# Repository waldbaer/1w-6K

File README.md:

# 1-Wire 6-Channel Binary Input Board using DS2411

A compact PCB providing six independent binary input channels on a 1-Wire bus, each based on a dedicated [DS2411](doc/ds2411.pdf) unique-ID device.
Prepared for use in standard 35 mm DIN-rail mounting enclosures.

## Hardware

### Schematic

see [1w-6K_schematic.pdf](doc/1w-6K_schematic.pdf).

### Rendering / Photo

### DIN-rail mounting

The PCB can be mounted to standard 35mm DIN rails using common _25mm DIN Rail Mounting Adapter_ with hole spacing of **12.5mm**.

## Key Features

* 6 × DS2411 devices connected to a the 1-Wire bus
  * Each DS2411 has its GND routed to an individual screw terminal.
  * A binary input channel is considered “closed” when its DS2411 (with factory-programmed 64-bit ROM ID) becomes visible on the bus.

* 1 additional DS2411 permanently connected to the bus.
  * Can be used for alive checks or bus identification

## How It Works

Each binary input corresponds to the GND line of one DS2411.
When GND is connected externally:

* The DS2411 becomes electrically active.
* Its globally unique 64-bit ID appears on the 1-Wire bus.
* The host system interprets this as input active / closed.

### Typical use cases

* Window open / closed detection
* Presence / absence detection

## Development

- PCB designed with [KiCad](https://www.kicad.org/)
- Production files created with KiCad plugin [KiCAD JLCPCB tools](https://github.com/Bouni/kicad-jlcpcb-tools)

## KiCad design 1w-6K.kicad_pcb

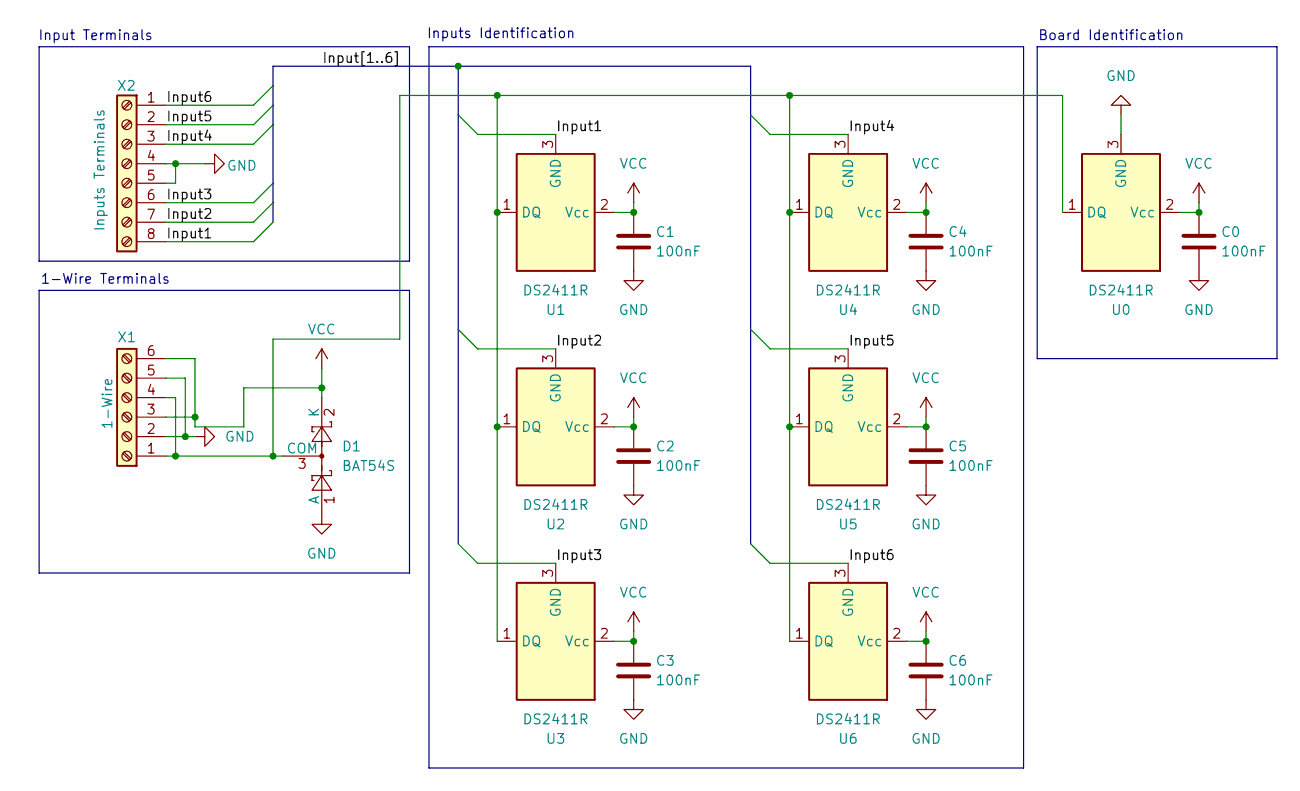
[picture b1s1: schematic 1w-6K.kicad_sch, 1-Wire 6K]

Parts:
C0, C1, C2, C3, C4, C5, C6: 100nF; C_0805_2012Metric
D1: BAT54S; SOT-23
U0, U1, U2, U3, U4, U5, U6: DS2411R; SOT-23-3
X1: 1-Wire; TerminalBlock_Phoenix_MKDS-1,5-6_1x06_P5.00mm_Horizontal
X2: Inputs Terminals; TerminalBlock_Phoenix_MKDS-1,5-8_1x08_P5.00mm_Horizontal

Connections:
/Input1: U1.3 (GND), X2.8
/Input2: U2.3 (GND), X2.7
/Input3: U3.3 (GND), X2.6
/Input4: U4.3 (GND), X2.3
/Input5: U5.3 (GND), X2.2
/Input6: U6.3 (GND), X2.1
GND: C0.2, C1.2, C2.2, C3.2, C4.2, C5.2, C6.2, D1.1 (A), U0.3 (GND), X1.2, X1.5, X2.4, X2.5
unnamed: D1.3 (COM), U0.1 (DQ), U1.1 (DQ), U2.1 (DQ), U3.1 (DQ), U4.1 (DQ), U5.1 (DQ), U6.1 (DQ), X1.1, X1.4
VCC: C0.1, C1.1, C2.1, C3.1, C4.1, C5.1, C6.1, D1.2 (K), U0.2 (Vcc), U1.2 (Vcc), U2.2 (Vcc), U3.2 (Vcc), U4.2 (Vcc), U5.2 (Vcc), U6.2 (Vcc), X1.3, X1.6

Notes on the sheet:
Inputs Identification
Board Identification
1-Wire Terminals
Input Terminals

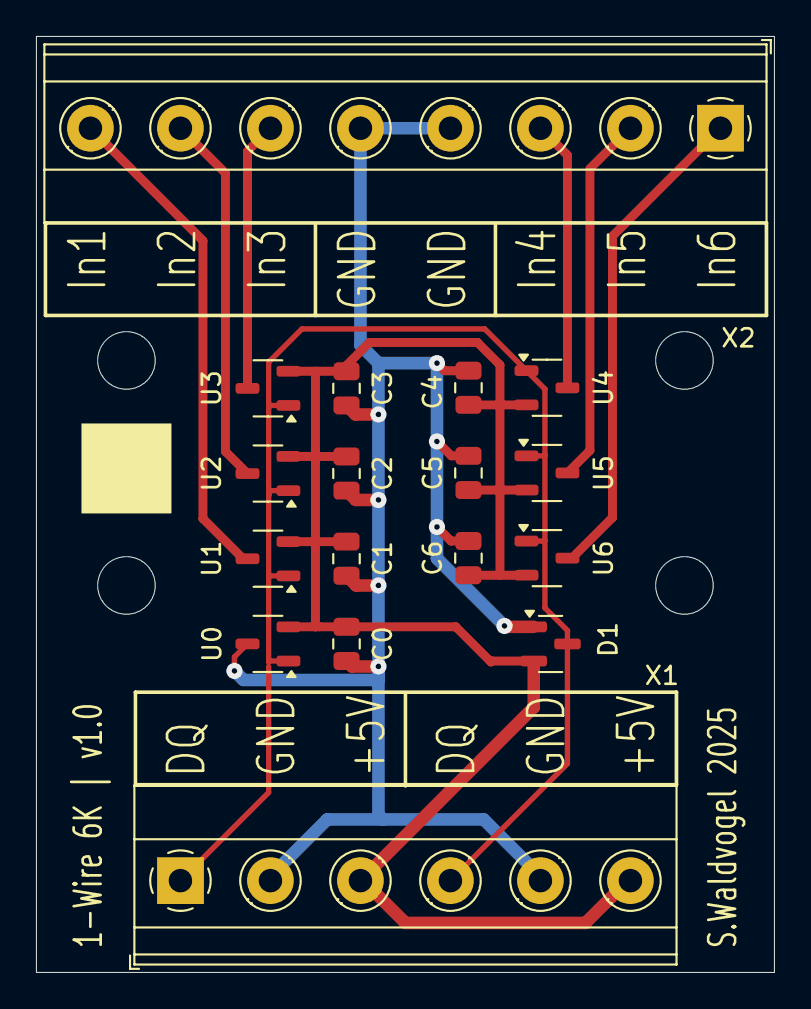
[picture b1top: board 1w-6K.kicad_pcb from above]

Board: 2 copper layers, 41.0 x 52.0 mm, 17 parts (0 on the bottom side), 9 nets.

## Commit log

2025-11-15 Publish 1w 6-K in version v1.0
2025-11-15 Updated schematic copyright & KiCad 8 -> 9
